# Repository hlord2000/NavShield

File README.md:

# An Arduino shield for the RKJXT1F42001 4-Axis Joystick w/ Encoder

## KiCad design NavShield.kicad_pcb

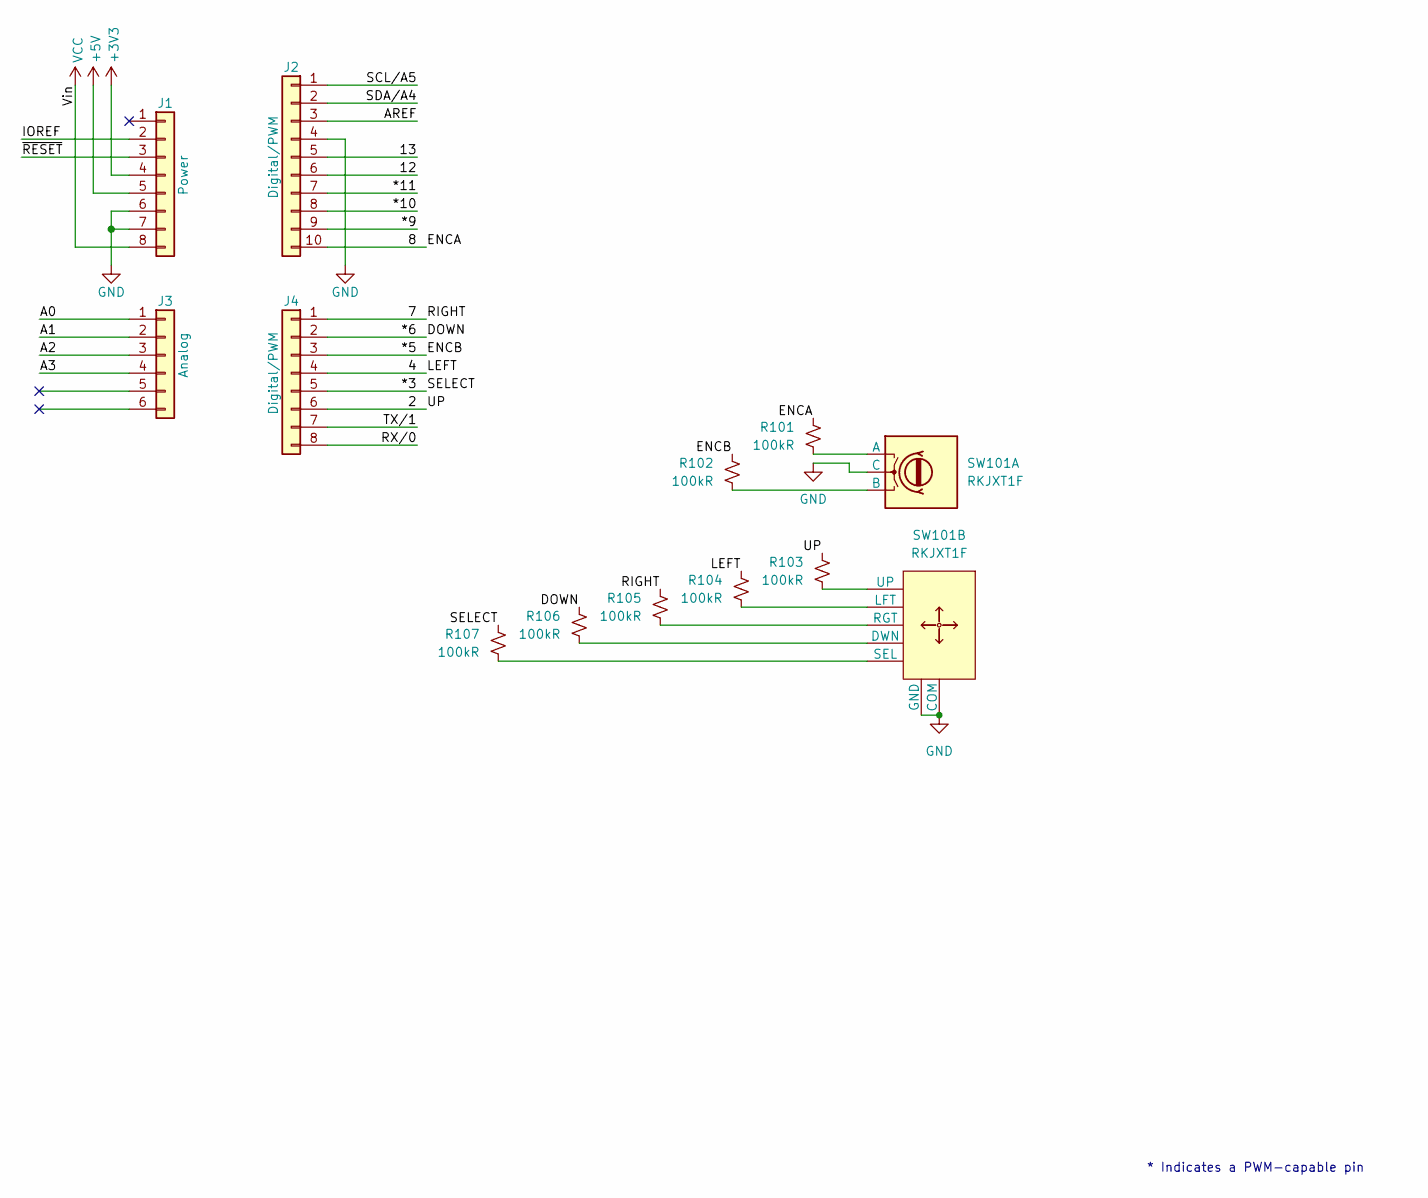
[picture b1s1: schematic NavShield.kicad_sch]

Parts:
J1: Power; PinHeader_1x08_P2.54mm_Vertical
J2: Digital/PWM; PinHeader_1x10_P2.54mm_Vertical
J3: Analog; PinHeader_1x06_P2.54mm_Vertical
J4: Digital/PWM; PinHeader_1x08_P2.54mm_Vertical
R101, R102, R103, R104, R105, R106, R107: 100kR; R_0402_1005Metric_Pad0.72x0.64mm_HandSolder
SW101: RKJXT1F

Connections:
+3V3: J1.4
+5V: J1.5
/2: J4.6, R103.1
/4: J4.4, R104.1
/7: J4.1, R105.1
/8: J2.10, R101.1
/12: J2.6
/13: J2.5
/*3: J4.5, R107.1
/*5: J4.3, R102.1
/*6: J4.2, R106.1
/*9: J2.9
/*10: J2.8
/*11: J2.7
/A0: J3.1
/A1: J3.2
/A2: J3.3
/A3: J3.4
/AREF: J2.3
/IOREF: J1.2
/RX/0: J4.8
/SCL/A5: J2.1
/SDA/A4: J2.2
/TX/1: J4.7
/~RESET: J1.3
GND: J1.6, J1.7, J2.4, SW101.2 (C), SW101.9 (COM), SW101.10 (GND)
unnamed: R101.2, SW101.1 (A)
unnamed: R102.2, SW101.3 (B)
unnamed: R106.2, SW101.7 (DWN)
unnamed: R104.2, SW101.5 (LFT)
unnamed: R105.2, SW101.6 (RGT)
unnamed: R107.2, SW101.8 (SEL)
unnamed: R103.2, SW101.4 (UP)
VCC: J1.8

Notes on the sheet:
* Indicates a PWM-capable pin

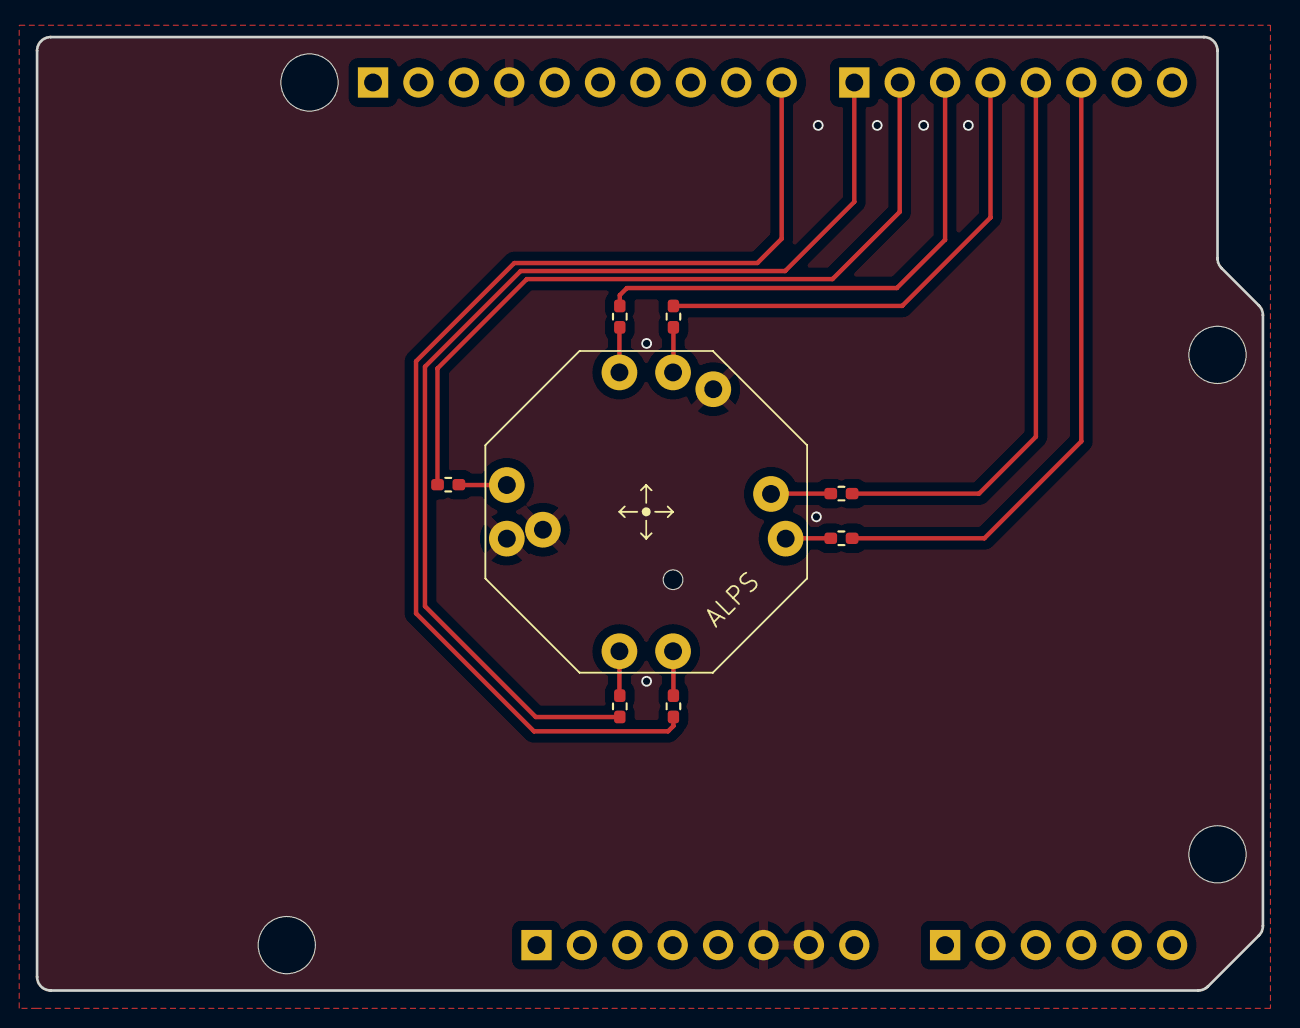
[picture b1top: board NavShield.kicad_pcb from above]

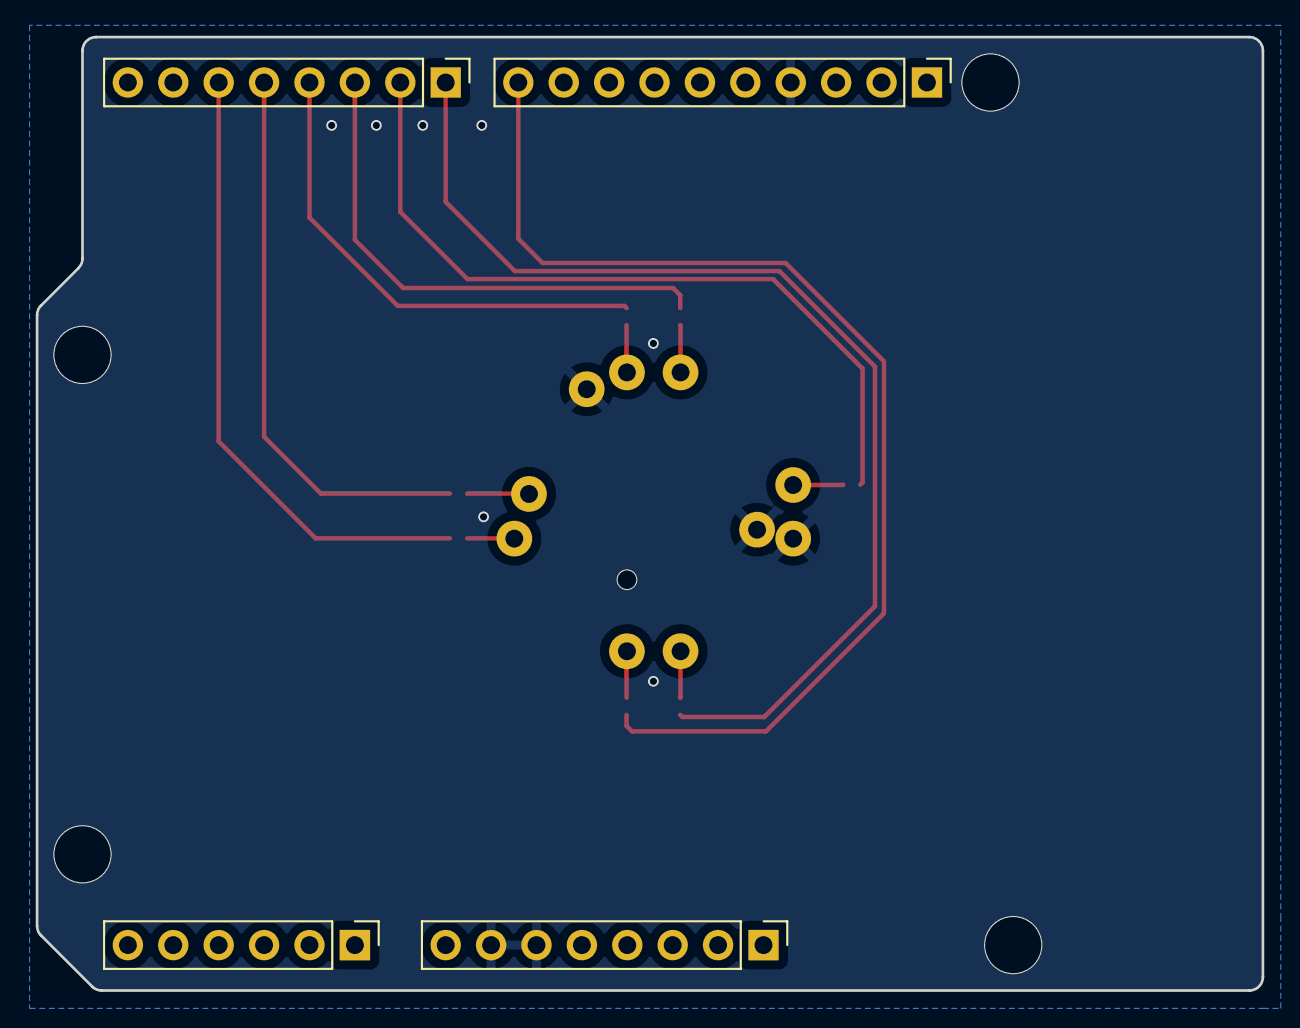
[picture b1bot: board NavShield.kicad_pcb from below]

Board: 2 copper layers, 68.6 x 53.3 mm, 16 parts (4 on the bottom side), 15 nets.

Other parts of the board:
MH1, MH2, MH3, MH4: MountingHole_3.2mm
